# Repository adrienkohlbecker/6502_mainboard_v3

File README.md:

# 6502 mainboard v3

## Board

## Schematic

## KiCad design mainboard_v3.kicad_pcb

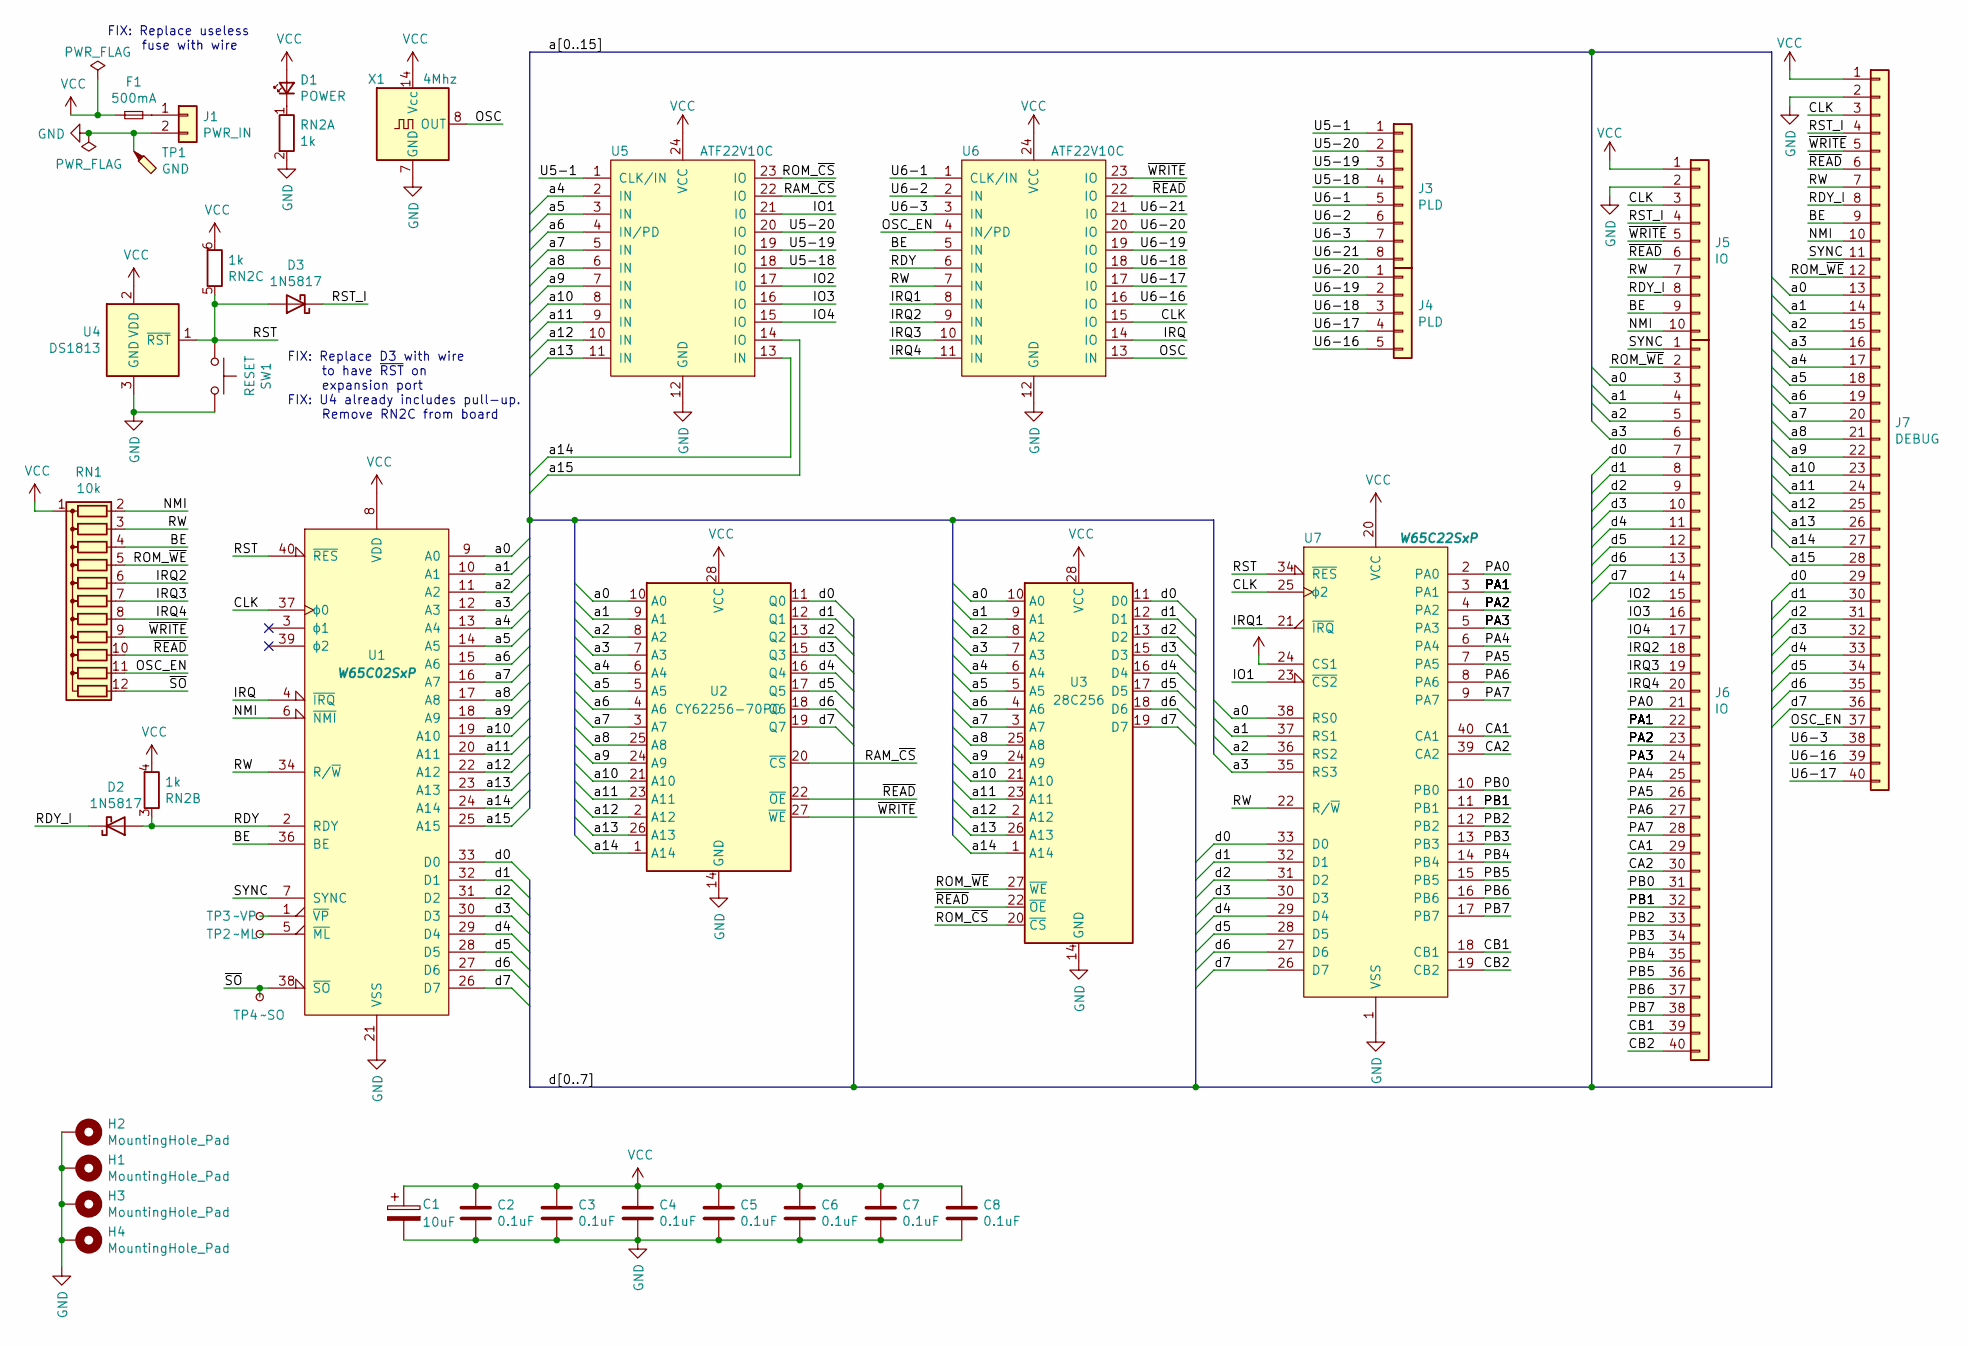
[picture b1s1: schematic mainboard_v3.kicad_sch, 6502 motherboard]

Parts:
C1: 10uF; CP_Radial_D6.3mm_P2.50mm
C2, C3, C4, C5, C6, C7, C8: 0.1uF; C_Disc_D3.0mm_W1.6mm_P2.50mm
D1: POWER; LED_D3.0mm
D2, D3: 1N5817; D_DO-41_SOD81_P7.62mm_Horizontal
F1: 500mA; Fuse_Littelfuse_372_D8.50mm
H1, H2, H3, H4: MountingHole_Pad; MountingHole_2.7mm_M2.5_DIN965_Pad
J1: PWR_IN; JST_EH_B2B-EH-A_1x02_P2.50mm_Vertical
J3: PLD; PinSocket_1x08_P2.54mm_Vertical
J4: PLD; PinSocket_1x05_P2.54mm_Vertical
J5: IO; PinHeader_1x10_P2.54mm_Vertical
J6: IO; PinHeader_1x40_P2.54mm_Vertical
J7: DEBUG; IDC-Header_2x20_P2.54mm_Vertical
RN1: 10k; R_Array_SIP12
RN2: 1k; R_Array_SIP6
SW1: RESET; SW_PUSH_6mm
TP1: GND; TestPoint_Loop_D2.60mm_Drill1.6mm_Beaded
TP2: ~ML; TestPoint_THTPad_D1.5mm_Drill0.7mm
TP3: ~VP; TestPoint_THTPad_D1.5mm_Drill0.7mm
TP4: ~SO; TestPoint_THTPad_D1.5mm_Drill0.7mm
U1: W65C02SxP; DIP-40_W15.24mm
U2: CY62256-70PC; DIP-28_W15.24mm
U3: 28C256; DIP_Socket-28_W11.9_W12.7_W15.24_W17.78_W18.5_3M_228-1277-0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
U4: DS1813; TO-92_Inline
U5, U6: ATF22V10C; DIP_Socket-24_W4.3_W5.08_W7.62_W10.16_W10.9_3M_224-5248-00-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
U7: W65C22SxP; DIP-40_W15.24mm
X1: 4Mhz; Oscillator_DIP-14

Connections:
/BE: J5.9, J7.9, RN1.4 (R3), U1.36 (BE), U6.5 (IN)
/CA1: J6.29, U7.40 (CA1)
/CA2: J6.30, U7.39 (CA2)
/CB1: J6.39, U7.18 (CB1)
/CB2: J6.40, U7.19 (CB2)
/CLK: J5.3, J7.3, U1.37 (ϕ0), U6.15 (IO), U7.25 (ϕ2)
/IO1: U5.21 (I0), U7.23 (~CS2)
/IO2: J6.15, U5.17 (I0)
/IO3: J6.16, U5.16 (IO)
/IO4: J6.17, U5.15 (IO)
/IRQ: U1.4 (~IRQ), U6.14 (IO)
/IRQ1: U6.8 (IN), U7.21 (~IRQ)
/IRQ2: J6.18, RN1.6 (R5), U6.9 (IN)
/IRQ3: J6.19, RN1.7 (R6), U6.10 (IN)
/IRQ4: J6.20, RN1.8 (R7), U6.11 (IN)
/NMI: J5.10, J7.10, RN1.2 (R1), U1.6 (~NMI)
/OSC: U6.13 (IN), X1.8 (OUT)
/OSC_EN: J7.37, RN1.11 (R10), U6.4 (IN/PD)
/PA0: J6.21, U7.2 (PA0)
/PA1: J6.22, U7.3 (PA1)
/PA2: J6.23, U7.4 (PA2)
/PA3: J6.24, U7.5 (PA3)
/PA4: J6.25, U7.6 (PA4)
/PA5: J6.26, U7.7 (PA5)
/PA6: J6.27, U7.8 (PA6)
/PA7: J6.28, U7.9 (PA7)
/PB0: J6.31, U7.10 (PB0)
/PB1: J6.32, U7.11 (PB1)
/PB2: J6.33, U7.12 (PB2)
/PB3: J6.34, U7.13 (PB3)
/PB4: J6.35, U7.14 (PB4)
/PB5: J6.36, U7.15 (PB5)
/PB6: J6.37, U7.16 (PB6)
/PB7: J6.38, U7.17 (PB7)
/RAM_~CS: U2.20 (~CS), U5.22 (IO)
/RDY: D2.2 (A), RN2.3 (R2.1), U1.2 (RDY), U6.6 (IN)
/RDY_I: D2.1 (K), J5.8, J7.8
/ROM_~CS: U3.20 (~CS), U5.23 (IO)
/ROM_~WE: J6.2, J7.12, RN1.5 (R4), U3.27 (~WE)
/RST: D3.2 (A), RN2.5 (R3.1), SW1.1, U1.40 (~RES), U4.1 (~RST), U7.34 (~RES)
/RST_I: D3.1 (K), J5.4, J7.4
/RW: J5.7, J7.7, RN1.3 (R2), U1.34 (R/~W), U6.7 (IN), U7.22 (R/~W)
/SYNC: J6.1, J7.11, U1.7 (SYNC)
/U5-1: J3.1, U5.1 (CLK/IN)
/U5-18: J3.4, U5.18 (IO)
/U5-19: J3.3, U5.19 (IO)
/U5-20: J3.2, U5.20 (IO)
/U6-1: J3.5, U6.1 (CLK/IN)
/U6-2: J3.6, U6.2 (IN)
/U6-3: J3.7, J7.38, U6.3 (IN)
/U6-16: J4.5, J7.39, U6.16 (IO)
/U6-17: J4.4, J7.40, U6.17 (I0)
/U6-18: J4.3, U6.18 (IO)
/U6-19: J4.2, U6.19 (IO)
/U6-20: J4.1, U6.20 (IO)
/U6-21: J3.8, U6.21 (I0)
/a0: J6.3, J7.13, U1.9 (A0), U2.10 (A0), U3.10 (A0), U7.38 (RS0)
/a1: J6.4, J7.14, U1.10 (A1), U2.9 (A1), U3.9 (A1), U7.37 (RS1)
/a2: J6.5, J7.15, U1.11 (A2), U2.8 (A2), U3.8 (A2), U7.36 (RS2)
/a3: J6.6, J7.16, U1.12 (A3), U2.7 (A3), U3.7 (A3), U7.35 (RS3)
/a4: J7.17, U1.13 (A4), U2.6 (A4), U3.6 (A4), U5.2 (IN)
/a5: J7.18, U1.14 (A5), U2.5 (A5), U3.5 (A5), U5.3 (IN)
/a6: J7.19, U1.15 (A6), U2.4 (A6), U3.4 (A6), U5.4 (IN/PD)
/a7: J7.20, U1.16 (A7), U2.3 (A7), U3.3 (A7), U5.5 (IN)
/a8: J7.21, U1.17 (A8), U2.25 (A8), U3.25 (A8), U5.6 (IN)
/a9: J7.22, U1.18 (A9), U2.24 (A9), U3.24 (A9), U5.7 (IN)
/a10: J7.23, U1.19 (A10), U2.21 (A10), U3.21 (A10), U5.8 (IN)
/a11: J7.24, U1.20 (A11), U2.23 (A11), U3.23 (A11), U5.9 (IN)
/a12: J7.25, U1.22 (A12), U2.2 (A12), U3.2 (A12), U5.10 (IN)
/a13: J7.26, U1.23 (A13), U2.26 (A13), U3.26 (A13), U5.11 (IN)
/a14: J7.27, U1.24 (A14), U2.1 (A14), U3.1 (A14), U5.13 (IN)
/a15: J7.28, U1.25 (A15), U5.14 (IO)
/d0: J6.7, J7.29, U1.33 (D0), U2.11 (Q0), U3.11 (D0), U7.33 (D0)
/d1: J6.8, J7.30, U1.32 (D1), U2.12 (Q1), U3.12 (D1), U7.32 (D1)
/d2: J6.9, J7.31, U1.31 (D2), U2.13 (Q2), U3.13 (D2), U7.31 (D2)
/d3: J6.10, J7.32, U1.30 (D3), U2.15 (Q3), U3.15 (D3), U7.30 (D3)
/d4: J6.11, J7.33, U1.29 (D4), U2.16 (Q4), U3.16 (D4), U7.29 (D4)
/d5: J6.12, J7.34, U1.28 (D5), U2.17 (Q5), U3.17 (D5), U7.28 (D5)
/d6: J6.13, J7.35, U1.27 (D6), U2.18 (Q6), U3.18 (D6), U7.27 (D6)
/d7: J6.14, J7.36, U1.26 (D7), U2.19 (Q7), U3.19 (D7), U7.26 (D7)
/~READ: J5.6, J7.6, RN1.10 (R9), U2.22 (~OE), U3.22 (~OE), U6.22 (IO)
/~SO: RN1.12 (R11), TP4.1, U1.38 (~SO)
/~WRITE: J5.5, J7.5, RN1.9 (R8), U2.27 (~WE), U6.23 (IO)
GND: C1.2, C2.2, C3.2, C4.2, C5.2, C6.2, C7.2, C8.2, H1.1, H2.1, H3.1, H4.1, J1.2, J5.2, J7.2, RN2.2 (R1.2), SW1.2, TP1.1, U1.21 (VSS), U2.14 (GND), U3.14 (GND), U4.3 (GND), U5.12 (GND), U6.12 (GND), U7.1 (VSS), X1.7 (GND)
unnamed: D1.1 (K), RN2.1 (R1.1)
unnamed: F1.2, J1.1
unnamed: TP2.1, U1.5 (~ML)
unnamed: TP3.1, U1.1 (~VP)
VCC: C1.1, C2.1, C3.1, C4.1, C5.1, C6.1, C7.1, C8.1, D1.2 (A), F1.1, J5.1, J7.1, RN1.1 (common), RN2.4 (R2.2), RN2.6 (R3.2), U1.8 (VDD), U2.28 (VCC), U3.28 (VCC), U4.2 (VDD), U5.24 (VCC), U6.24 (VCC), U7.20 (VCC), U7.24 (CS1), X1.14 (Vcc)

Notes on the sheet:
FIX: Replace D3 with wire to have ~{RST} on expansion port FIX: U4 already includes pull-up. Remove RN2C from board
FIX: Replace useless fuse with wire

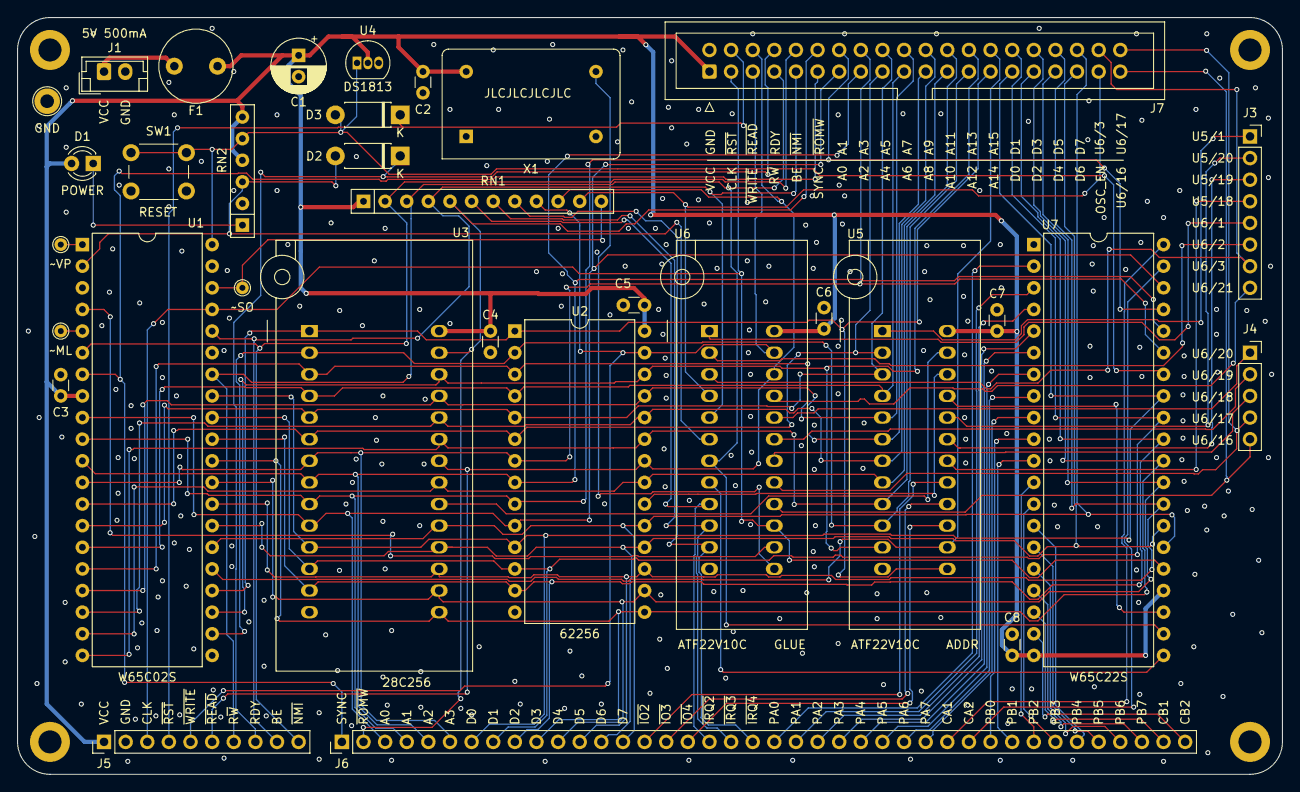
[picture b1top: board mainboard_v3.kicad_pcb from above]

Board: 4 copper layers, 148.6 x 88.9 mm, 37 parts (0 on the bottom side), 89 nets.

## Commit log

2021-05-30 Add mainboard v3
2021-12-13 Mainboard v3
2021-12-19 Remove ignored files
2023-06-06 Migrate to KiCad 6
2023-06-06 Add schematic
2023-06-06 Add readme
2023-06-07 Add WinCUPL files
2023-06-10 Fix schematic
